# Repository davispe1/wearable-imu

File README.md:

# Wearable IMU — Project Master README

> Wearable IMU-based motion-capture system for **live upper-limb pose estimation**.
> Summer research project (IIT Chicago), with the goal of publishing.
>
> Single source of truth for the system architecture, hardware, communication design,
> processing pipeline, and repository structure.

### At a glance

| Node PCB (v1.0) | 5-DOF calibration / teleop rig |
|---|---|
|  |  |

**Left:** the wearable IMU node PCB (STM32WB55CEUx + DWM3000 + LSM6DSV16BXTR + BMM350).
**Right:** a separate parallel sub-project, [`test-rig/`](test-rig/README.md) — a
motorised 5-DOF arm used two ways: (1) **teleoperation demo**, driven live from the
wearable nodes, and (2) **calibration / ground truth**, moved through known joint
angles to validate the IMU pipeline's estimated angles against a known reference.

> **New to this project?** The actively maintained TODO / open-work list is
> [`docs/07-roadmap.md`](docs/07-roadmap.md) — start there to see what's done, what's
> open, and what's missing before picking up work.

---

## 1. Project overview

A network of small body-worn **IMU nodes** streams motion data to a **PC**, which reconstructs
and displays a live 3D skeleton of the upper limb. The design philosophy is **thin nodes,
heavy PC**: nodes only sample and transmit; all fusion, kinematics, and visualization run on
the PC — a discrete GPU is recommended for the live 3D visualization but not strictly required.

| Item | Decision (v1) |
|------|----------------|
| Focus | Upper limb |
| Output | Live joint angles + 3D skeleton visualization |
| Nodes | Scalable design; initial bring-up on **2 confirmed nodes** (wrist, clavicle), a 3rd (chest) possible, scaling to **6–8** |
| Sample rate | **100 Hz** target (hardware capable to 200 Hz) |
| Environment | Lab / bench (PC present in the room) |
| Compute | All heavy processing on the PC, **not** on a body MCU |
| Reference work | *Ultra Inertial Poser* (UIP), SIGGRAPH 2024 — see [References](#10-references) |

---

## 2. System architecture

All nodes use **identical hardware** (STM32WB55CEUx + DWM3000). One node is designated the
**master** purely in firmware. Because the boards are identical, multiple transport
topologies can be tested and compared on the same hardware (a useful experimental result).

### Primary topology

```mermaid
flowchart LR
    subgraph Body["On-body (wearable)"]
        N1["Sensor node 1<br/>WB55CE + DWM3000"]
        N2["Sensor node 2<br/>WB55CE + DWM3000"]
        N3["Sensor node N<br/>WB55CE + DWM3000"]
        M["Master node<br/>WB55CE + DWM3000"]
        N1 -- UWB --> M
        N2 -- UWB --> M
        N3 -- UWB --> M
    end
    M -- "BLE" --> PC["PC<br/>all processing + 3D viewer"]
    M -. "SWD / SWO (wired dev/recovery)" .-> PC
```

- **On-body UWB network** carries node data to the master, provides **time sync**, and
  (phase 2) provides **inter-node ranging** for drift correction.
- **Master node** aggregates all node data and is the single uplink to the PC.
- **PC** runs the full pipeline and the live visualization (stages detailed in [§6](#6-processing-pipeline-pc)).

> **v1 needs no Kalman filter.** Orientation → joint angles → DH skeleton → render is a
> complete working visualization. The EKF (with UWB distances) is a phase-2 enhancement
> for drift and position.

---

## 3. Transports & fallbacks

Every node has **two radios**: UWB for the on-body network (node → master, time sync,
ranging) and BLE for the master's wireless uplink to the PC. Paths to the PC:

| Layer | Path | Role |
|-------|------|------|
| Live | BLE (master → PC, **host-native** Bluetooth) | Main wireless link |
| Wired | **SWD / SWO** via ST-LINK, or native USB (CDC) | Bench/dev + data recovery |

Notes:
- BLE uses **serial-over-BLE** (a transparent UART-style GATT service / NUS-equivalent), so
  it behaves like a wireless UART. **Decided: host-native Bluetooth** — the PC's own
  Bluetooth receives it, no extra receiver hardware.
- **Debug/data connection is a TC2030-IDC footprint** — bare pogo-pin pads on the PCB, not a
  soldered connector. A separate Tag-Connect TC2030 cable/clip clamps onto those pads from
  outside the board (to an ST-LINK) to make contact. Carries SWDIO/SWDCLK/SWO; SWO gives a
  one-way MCU→PC data channel (read via SWV tooling).
- **USB-C carries both charging and native USB data** (the WB55CEUx has native USB; a USB
  CDC stack is already in `firmware/USB_Device/`). The bring-up smoke test is likely read
  over this USB-CDC port, not SWO — **needs confirming**, since earlier wording assumed
  SWD/SWO was the only wired data path.
- RAM ring buffer (~seconds) covers jitter/retransmit; a >3–5 s dropout is treated as a
  compromised session regardless, so heavy persistence is unnecessary.

---

## 4. Hardware — Node BOM

Single identical board for every node. The architecturally significant parts:

| Function | Part | Notes |
|----------|------|-------|
| MCU | **STM32WB55CEUx** (UFQFPN48) | Dual-core: Cortex-M4 @ 64 MHz (application) + Cortex-M0+ @ 32 MHz (radio stack), Bluetooth 5.4 LE + 802.15.4, 512 KB flash, 256 KB SRAM, native USB. Drives DWM3000 over SPI. |
| IMU | **LSM6DSV16BXTR** | 6-axis, onboard SFLP sensor fusion. **I2C1, addr `0x6B`** (SDO pulled high) |
| Magnetometer | **BMM350** | Separate 3-axis → makes the node 9-DOF. **Decided: using it for v1** (not yet implemented in firmware — see [§7](#7-build-phases--roadmap)). **I2C1, addr `0x14`** (ADSEL pulled low) |
| UWB | **DWM3000** | Data transport + sync + (phase-2) inter-node ranging. SPI1 (only SPI sensor on the node — IMU and mag are both I2C) |

Full parts list (power management, connectors, battery, indicator, etc.) is in
[`hardware/electronics/v1.0/README.md`](hardware/electronics/v1.0/README.md#key-parts),
sourced directly from the fabricated board's BOM.

### PC-side hardware

| Function | Part | Notes |
|----------|------|-------|
| BLE receiver | **PC-native Bluetooth** | No extra receiver hardware |
| Compute | Any PC (a discrete GPU helps for the live 3D visualization, not required) | Runs full pipeline + visualization |

### Node PCB v1.0 — renders & board views

> Full detail (all four copper layers, schematic PDF, fab files) lives in
> [`hardware/electronics/v1.0/`](hardware/electronics/v1.0/README.md).
> Known antenna keepout issue on the DWM3000 — see [§7](#7-build-phases--roadmap) for the
> decision on whether that becomes a v1.1 bug-fix spin or gets folded into a v2.0 redesign,
> pending v1.0 bring-up results. See also
> [`hardware/electronics/CHANGELOG.md`](hardware/electronics/CHANGELOG.md).

| PCB 3D — top | PCB 3D — bottom |
|---|---|
|  |  |

| Assembled (exploded) | Worn on wrist |
|---|---|
|  |  |

---

## 5. Communication & protocols

### Data format (per node, per sample)
- **Option A (preferred for the rig): raw 9-DOF** — accel(3) + gyro(3) + mag(3) + timestamp.
  Maximum flexibility; host does all fusion. ~40 bytes/sample.
- **Option B: SFLP quaternion** (from the LSM6DSV16B) + raw mag. Smaller, less host work.
- **Decision: open** (see [Open items](#11-open-items)). Magnetometer rate can be lower
  (e.g., 50–100 Hz).

> Bandwidth budgeting and UWB TDMA scheduling design used to be spelled out here with
> specific numbers, but neither BLE nor UWB has actually been tested on hardware yet — those
> numbers were pre-hardware-test estimates, not decisions. They now live in
> [`docs/04-firmware.md`](docs/04-firmware.md#tdma-frame-planned--not-implemented) (UWB
> scheduling/sync) and [`docs/03-communication.md`](docs/03-communication.md#6-bandwidth-check)
> (bandwidth), clearly marked as unvalidated estimates rather than settled numbers.

---

## 6. Processing pipeline (PC)

| Stage | Purpose | Maps to known technique |
|-------|---------|--------------------------|
| 0. Calibration | Sensor-to-segment alignment (T/N-pose) | — |
| 1. Orientation filter | accel+gyro(+mag) → world-frame quaternion | complementary / Madgwick / VQF (or use SFLP) |
| 2. Joint angles | relative rotation between adjacent segments | rotation matrices / quaternions |
| 3. EKF (phase 2) | fuse UWB inter-node distances → fix drift / get positions | Kalman filter (new) |
| 4. Forward kinematics | joint angles + segment lengths → 3D skeleton | **Denavit-Hartenberg** |
| 5. Visualization | live render of links/joints | 3D viewer |

- **v1 path:** stages 0 → 1 → 2 → 4 → 5 (no EKF).
- **Phase 2:** insert stage 3 (EKF + UWB ranging) for drift/position.
- A **synthetic data generator** (or arm-simulator rig) can drive the pipeline before
  hardware is ready.

---

## 7. Build phases / roadmap

1. **Firmware + data path** — node sampling, UWB schedule, master aggregation, PC ingest.
   Bring up over **SWD/SWO (wired)** first (familiar tooling), then add BLE as a parallel path.
2. **Visualization program** — orientation → joint angles → DH skeleton → live 3D render.
   Develop against **synthetic data** first. No Kalman filter needed.
3. **EKF** — learn the Kalman filter (from complementary-filter intuition) and fold in the
   UWB inter-node distances for drift/position.

> BLE de-risking: prove the entire system over wired (SWD/SWO) first; learn BLE in isolation
> on a NUCLEO-WB55RG with ST's serial-over-BLE example; then integrate with the wired path
> still available as a safety net.

### Parallel workstream — 5-DOF arm / test rig

A 5-DOF robotic arm mirroring human upper-limb kinematics. It's a single physical
rig serving **two purposes**:

1. **Teleoperation demo** — drive the arm live from the wearable IMU nodes.
2. **Calibration / ground-truth measurement** — move the arm through known joint
   angles and compare against the IMU pipeline's estimated angles, to quantify
   filter error.

Status: forward kinematics validated (MATLAB GUI); inverse kinematics implemented
but not yet validated; mechanical CAD for the rig itself in progress. Full detail
in [`docs/07-roadmap.md`](docs/07-roadmap.md#parallel-workstream--5-dof-arm-teleoperation--calibration-rig)
and [`test-rig/README.md`](test-rig/README.md).

---

## 8. Repository structure

Actual current tree (not aspirational — status noted per folder):

```
wearable-imu/
├── README.md                      # this file
├── CONTRIBUTING.md                # branch/tag/versioning conventions
├── docs/                          # markdown source of truth, one file per section
│   ├── 01-system-overview.md
│   ├── 02-hardware.md
│   ├── 03-communication.md        # authoritative wire protocol spec
│   ├── 04-firmware.md             # firmware architecture: CubeMX project + smoke test are
│   │                               #   real; packet/comms application layer still planned
│   ├── 05-host-pipeline.md
│   ├── 06-calibration.md
│   ├── 07-roadmap.md              # build phases, real done/not-done status, open items
│   ├── 08-appendices.md
│   └── 09-tools.md                # tools used to build/assemble hardware — incomplete
│
├── firmware/                      # STM32CubeIDE project for the STM32WB55CEUx node
│   ├── Core/                      # CubeMX-generated (HAL, startup, clock) — do not hand-edit
│   ├── Drivers/                   # CMSIS + STM32WBxx HAL
│   ├── Middlewares/ST/            # ST middleware
│   ├── ThirdParty/                # BMM350, lsm6dsv16bx vendor drivers
│   ├── USB_Device/                # USB CDC (virtual COM port) stack — native USB, not charging-only
│   └── *.ioc / *.ld               # CubeMX config + linker scripts
│   (application logic — packet serializer, UWB TDMA, BLE serial, role state
│    machines — not written yet; see docs/07-roadmap.md)
│
├── host/                          # Python package — the live PC pipeline
│   └── wearable_imu/
│       ├── ingest/                # serial / SWO readers + wire protocol codec (real, tested)
│       ├── sync/                  # timebase alignment
│       ├── orientation/           # filters (complementary / Madgwick / VQF) — stub
│       ├── kinematics/            # joint angles + DH forward kinematics — stub
│       ├── ekf/                   # phase 2: UWB-distance fusion — stub
│       ├── viz/                   # 3D skeleton viewer — stub
│       ├── sim/                   # synthetic data generator (real, drives dev without hardware)
│       ├── config.py
│       └── main.py
│
├── hardware/                      # physical design files — only place with version folders
│   ├── electronics/v1.0/          # node PCB: schematic, layout, fab files, renders
│   └── mechanical/v1.0/           # node enclosure: STEP/STL, assembly renders
│
├── simulation/scripts/            # 5-DOF arm kinematics (MATLAB) — FK validated, IK
│                                   # implemented pending validation. Not yet cross-linked
│                                   # into test-rig/ below.
├── test-rig/                      # ground-truth validation rig — mostly planned
│   └── hardware/mechanical/v1.0/  # rig arm CAD — in progress (the only real part so far)
│
├── calibration/                   # calibration routines + saved profiles — planned
└── tools/                         # flash/capture/calibrate/replay scripts — planned
```

---

## 9. Design decisions log (the "why")

- **Sensor selection, generally:** across the BOM, the guiding principle was to pick the
  most capable part available in its class at design time, not the cheapest one that
  technically works — this is a research/publication project, not a cost-optimized
  product, so headroom (accuracy, noise floor, ranging precision) was prioritized over
  BOM cost. The three sensing ICs below were each chosen on that basis:
  - **IMU = LSM6DSV16BXTR:** one of ST's most capable 6-axis parts at selection time —
    onboard SFLP (Sensor Fusion Low Power) hardware fusion can offload orientation
    estimation from the host, but is bypassable for a raw-data path if the host EKF is
    preferred instead. High ODR headroom (only 120 Hz is used here).
  - **Magnetometer = BMM350:** chosen for resolution/noise performance over cheaper
    3-axis parts, making the node 9-DOF. Populated on every board, but use is **optional**
    pending characterization of the lab's magnetic environment — indoor steel/motors can
    make magnetometer data actively worse than leaving it out.
  - **UWB = DWM3000:** the most capable UWB module available for this application —
    supports the newer 802.15.4z standard (better multipath resistance) with strong
    ranging accuracy. Chosen as the **sole radio** on the node: it replaces what would
    otherwise be a separate ranging radio, handling data transport, sub-ns time sync,
    and inter-node ranging in one part.
- **MCU = STM32WB55CEUx** (over the earlier L431 / U535): the master needs BLE; identical
  BLE-capable boards let any node be master and enable topology testing. Dual-core
  (Cortex-M4 app core + Cortex-M0+ radio stack core), ultra-low-power (good for a small
  battery), and has native USB (unlike the STM32WBA55 originally assumed during design —
  see the note in [§3](#3-transports--fallbacks) about reconciling the SWD/SWO-vs-USB wired
  data path now that native USB is actually available).
- **Master-aggregator + single BLE uplink** (vs UIP's per-node BLE): one BLE link instead of
  N (avoids PC multi-link flakiness) and gives tighter on-body sync.
- **BLE for the PC uplink, UWB kept on-body:** the master's single link to the PC is BLE
  (2.4 GHz, more robust to body blocking than UWB's 6.5–8 GHz); UWB is reserved for the
  on-body network — data transport to the master, time sync, and ranging — where it's
  irreplaceable.
- **PC does all heavy compute** (not a body MCU): the pipeline (and future ML) is GPU/
  desktop work, and PC-side iteration is far faster than reflashing firmware.
- **No on-node SD card or flash IC:** RAM buffer only; avoids tedious card extraction, and
  the fabricated v1.0 board doesn't populate a flash chip at all — recovery happens over
  SWD (or USB, pending the reconciliation above).
- **100 Hz for v1:** matches UIP and is sufficient for full-body pose; keeps BLE bandwidth
  comfortable.

---

## 10. References

- **[Ultra Inertial Poser (UIP), SIGGRAPH 2024](https://siplab.org/projects/UltraInertialPoser)**
  (Armani, Qian, Jiang, Holz — [ACM DL](https://dl.acm.org/doi/10.1145/3641519.3657465),
  [arXiv](https://arxiv.org/abs/2404.19541),
  [code](https://github.com/eth-siplab/UltraInertialPoser)) — sparse body-worn IMU + UWB
  inter-node ranging, fused on a host with VQF orientation, per-pair EKF, an LSTM + graph-conv
  network, and a physics dynamics optimizer to produce full-body pose.
  - **This project mirrors** the IMU + UWB sensing approach and the "thin nodes, host does
    the work" philosophy.
  - **This project differs:** adds a magnetometer (9-DOF vs UIP's 6-DoF); uses a
    master-aggregator UWB→BLE topology (vs UIP's per-node BLE to host); focuses on upper-limb
    joint angles + live visualization for v1; EKF/ranging is a phase-2 enhancement.

---

## 11. Open items

**The actively maintained TODO / open-work list lives in
[`docs/07-roadmap.md`](docs/07-roadmap.md)** — its "Open items", "Hardware revisions", and
"Known gaps" sections are the source of truth for what's decided, what's still open, and
what's missing (including firmware, UWB/BLE testing, the test-rig end-effector adapter, and
the onboarding doc for new students). This section is intentionally just a short pointer
rather than a second list, to avoid the two drifting out of sync.

Top-level decisions still open, at a glance:
- **Data format:** raw 9-DOF vs SFLP quaternion + raw mag.
- **Magnetometer:** whether to use it (characterize the lab's magnetic environment first;
  hardware is populated either way).
- **Sample rate:** confirm 100 Hz (vs 200 Hz).

---

## How to use this document

This README and the `docs/` folder are the **markdown source of truth** (versioned in git;
diagrams in **Mermaid** so they edit as text and render on GitHub). For a polished copy for
the team/professor, export markdown → Word/PDF with Pandoc rather than hand-maintaining a
second copy.

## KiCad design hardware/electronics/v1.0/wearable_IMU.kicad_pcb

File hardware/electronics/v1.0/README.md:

# electronics / v1.0

Node PCB — revision 1.0. 4-layer board (F.Cu, In1.Cu, In2.Cu, B.Cu).

> **Known issue, fix path pending v1.0 evaluation:** the DWM3000 UWB antenna
> placement doesn't fully follow Qorvo's layout guidelines (clearance/keepout,
> feed line length), which may affect range/link margin. Whether this becomes a
> v1.1 placement-only fix or gets folded into a v2.0 redesign depends on how
> v1.0 performs in bring-up. See `../CHANGELOG.md` and `docs/07-roadmap.md`.

## Contents

- `wearable_IMU.kicad_sch` — schematic (source)
- `wearable_IMU.kicad_pcb` — layout (source)
- `wearable_IMU.kicad_pro` / `.kicad_prl` — project files
- `documentation/` — exported images (below) + `schematic.pdf`
- `jlcpcb/` — fab outputs: `gerber/` (raw Gerbers + drill files), `production_filesV1.0/`
  (BOM, pick-and-place, zipped Gerbers — the JLCPCB submission set), `project.db`
- `fabrication-toolkit-options.json` — KiCad fabrication-toolkit plugin export settings
- The PCB's 3D model (`PCB.step`) lives in `../../mechanical/v1.0/` alongside the
  enclosure — kept in one place instead of duplicated here

Cleaned up (untracked, safe to regenerate/ignore): KiCad's local autosave/history
folders (`.history/`, `.history_trim/` — an embedded git history plugin, ~290 MB),
`wearable_IMU-backups/` (autosave zips), a stale `production/` test export
("prueba1"), an empty `jlcpcb/production_files/`, 0-byte `.rpt` temp files, and
KiCad's `.lck` lock files. Added patterns to `.gitignore` so these don't come back.

## Key parts

Straight from the fabricated board's BOM (`jlcpcb/production_filesV1.0/BOM-wearable_IMU.csv`):

| Function | Part |
|----------|------|
| MCU | STM32WB55CEUx |
| IMU | LSM6DSV16BXTR |
| Mag | BMM350 |
| UWB | DWM3000 |
| SMPS | TPSM828224 |
| Charger | BQ25185 |
| Fuel gauge | MAX17048G+T10 |
| Power btn | STM6601BM2DDM6F |

No flash IC is populated — RAM buffering only, no on-node session logging.

## Fabrication

Board fabricated and assembled via **JLCPCB** (PCBA — SMT assembly included, not just bare
board fab). Production files were exported from KiCad using the **fabrication-toolkit**
plugin (`fabrication-toolkit-options.json` holds its export settings).

To re-order or fab a new revision:
1. Open `wearable_IMU.kicad_pro` in KiCad, update as needed.
2. Run the fabrication-toolkit plugin to regenerate `jlcpcb/production_filesV1.0/` (or a new
   `production_filesVX.Y/` for a new revision) — Gerbers, `BOM-wearable_IMU.csv`,
   `CPL-wearable_IMU.csv` (component placement).
3. Upload the zipped Gerbers + BOM + CPL to JLCPCB's PCBA order flow.

## Board renders & layers

**3D views**

| Top | Bottom |
|---|---|
|  |  |

**Copper layers** (top → bottom of stack)

| F.Cu (top) | In1.Cu | In2.Cu | B.Cu (bottom) |
|---|---|---|---|
|  |  |  |  |

**Schematic:** [`documentation/schematic.pdf`](documentation/schematic.pdf)

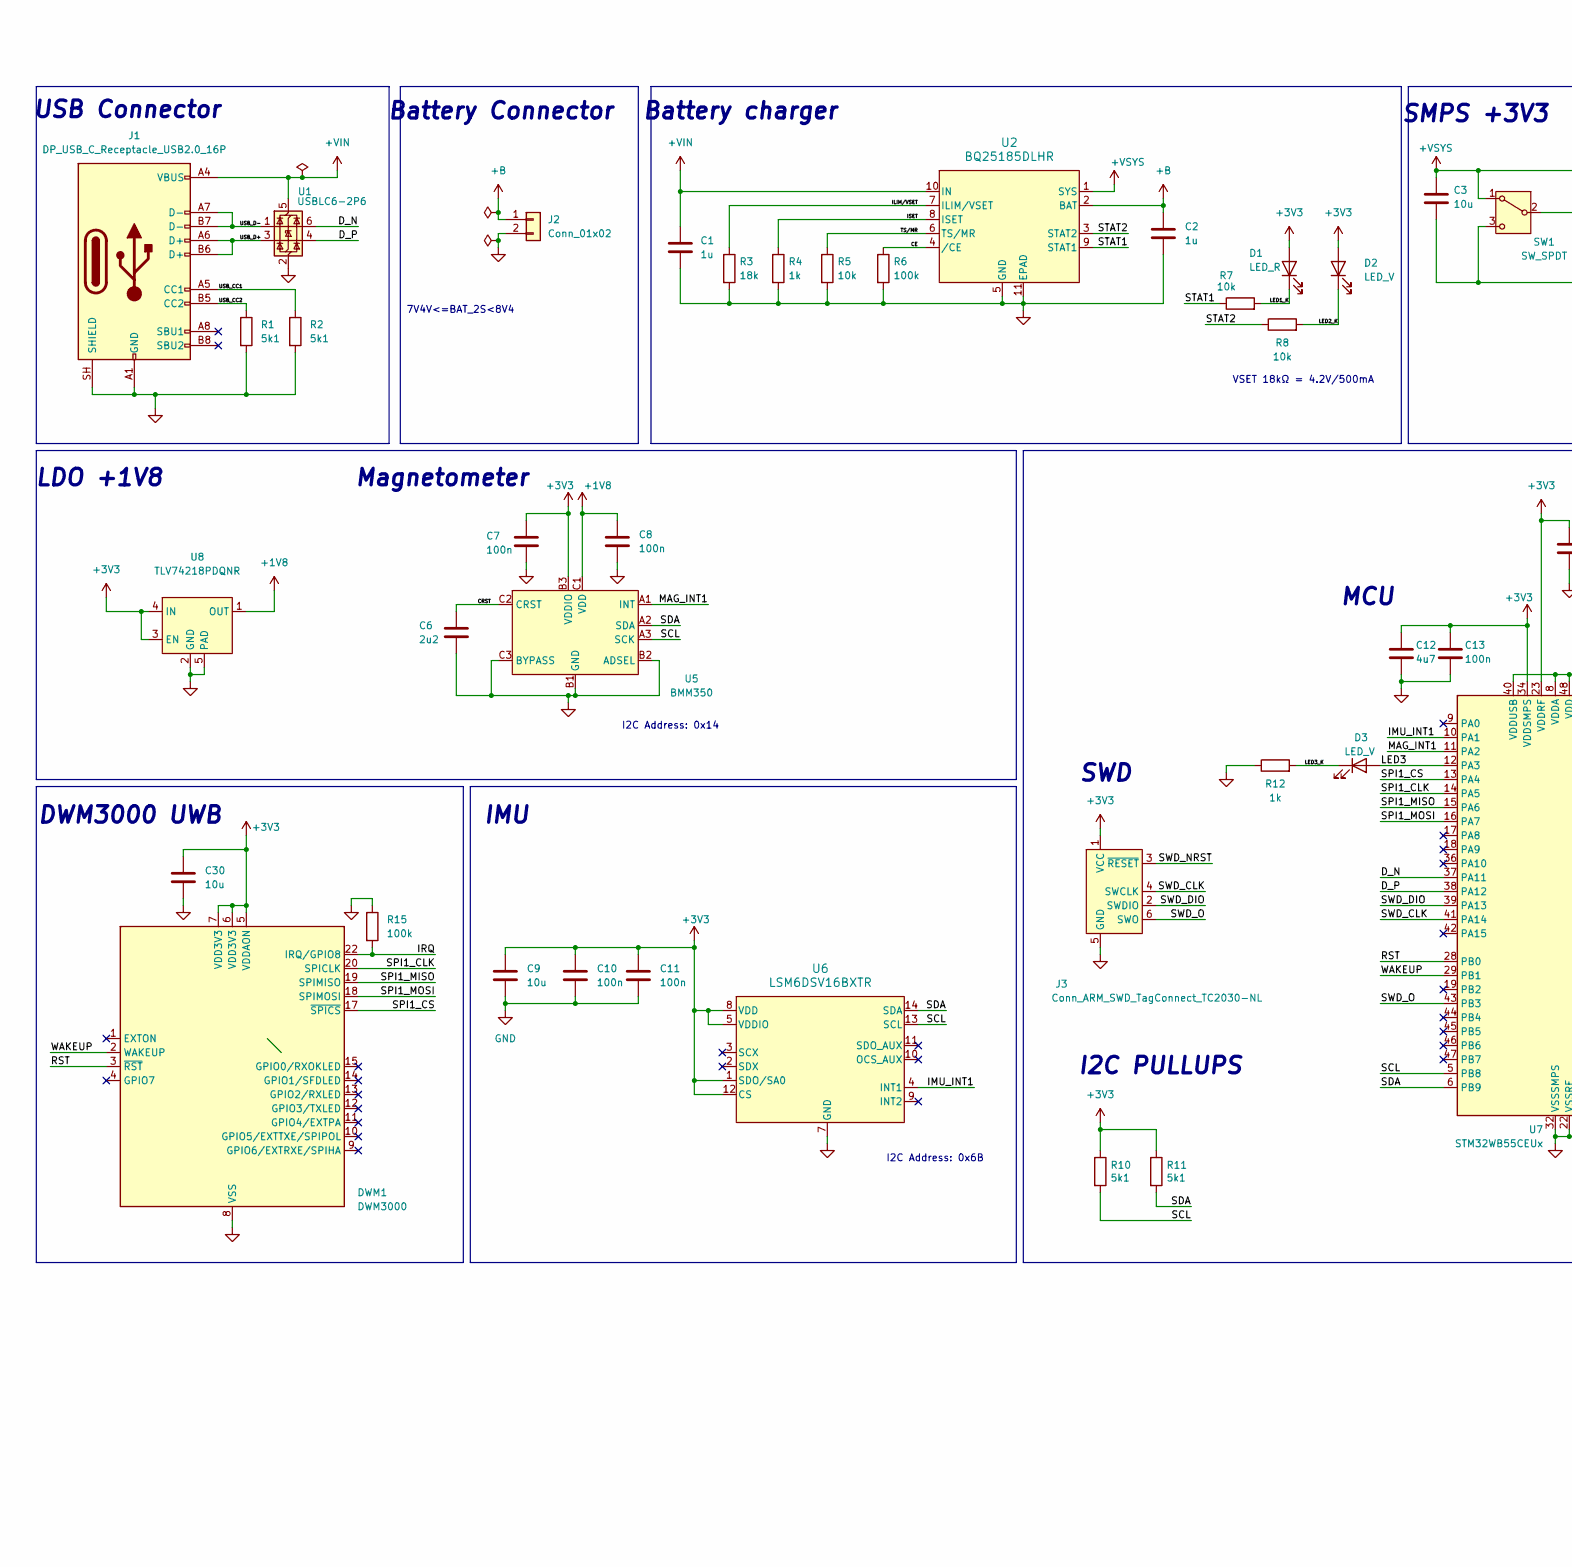
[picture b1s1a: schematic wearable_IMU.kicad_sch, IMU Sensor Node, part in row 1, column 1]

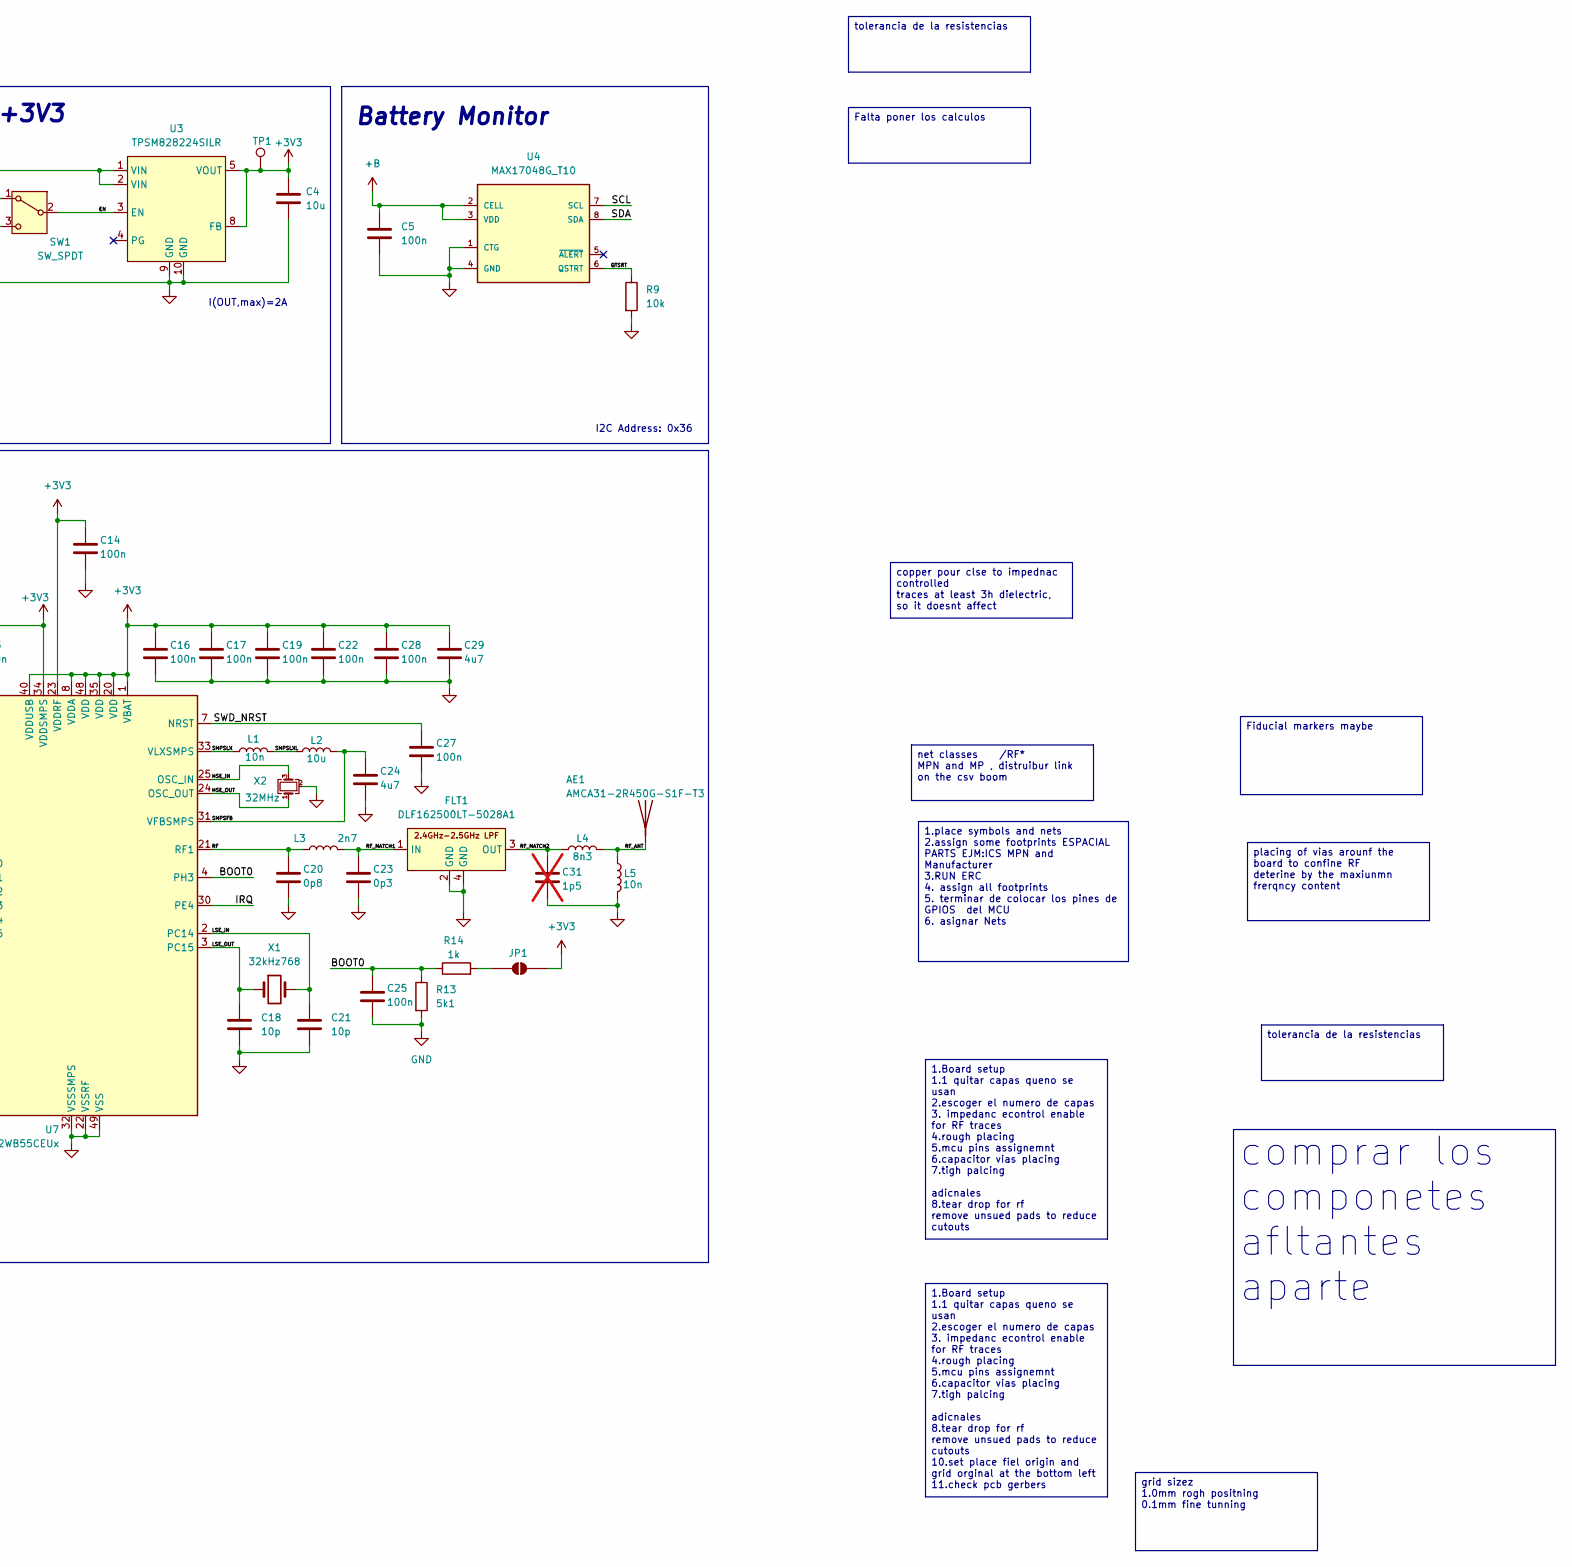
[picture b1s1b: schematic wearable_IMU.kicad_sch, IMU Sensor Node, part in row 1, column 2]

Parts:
AE1: AMCA31-2R450G-S1F-T3; XDCR_AMCA31-2R450G-S1F-T3; MPN AMCA31-2R450G-S1F-T3
C1, C2: 1u; C_0402_1005Metric
C3, C4, C9, C30: 10u; C_0603_1608Metric
C5, C7, C8, C10, C11, C13, C14, C16, C17, C19, C22, C25, C27, C28: 100n; C_0402_1005Metric
C6: 2u2; C_0402_1005Metric; MPN 0805YC225KAT2A
C12, C29: 4u7; C_0603_1608Metric
C18, C21: 10p; C_0402_1005Metric
C20: 0p8; C_0402_1005Metric; MPN GRM1555C1HR80BA01D
C23: 0p3; C_0402_1005Metric; MPN GRM1555C1HR30WA01D
C24: 4u7; C_0603_1608Metric; MPN GRM155R60J475KE19
C31: 1p5; C_0402_1005Metric; not fitted
D1: LED_R; LED_0402_1005Metric
D2, D3: LED_V; LED_0402_1005Metric
DWM1: DWM3000; MPN DWM3000TR13
FLT1: DLF162500LT-5028A1; FILTER-SMD_0603-4P-L1.6-W0.8-L-1; MPN DLF162500LT-5028A1; LCSC Part C531364
J1: DP_USB_C_Receptacle_USB2.0_16P; DP_USB_C_Receptacle_GCT_USB4105-xx-A_16P_TopMnt_Horizontal
J2: Conn_01x02; JST_SH_SM02B-SRSS-TB_1x02-1MP_P1.00mm_Horizontal
J3: Conn_ARM_SWD_TagConnect_TC2030-NL; Tag-Connect_TC2030-IDC-NL_2x03_P1.27mm_Vertical
JP1: SolderJumper_2_Open; SolderJumper-2_P1.3mm_Open_RoundedPad1.0x1.5mm
L1: 10n; L_0402_1005Metric; LCSC Part C445746
L2: 10u; L_0805_2012Metric; MPN LQM21FN100M70L; LCSC Part C162582
L3: 2n7; L_0402_1005Metric; LCSC Part C113054
L4: 8n3; L_0402_1005Metric; MPN LQW15AN8N3C10D; LCSC Part C412363
L5: 10n; L_0402_1005Metric; MPN LQW15AN9N7G00D; LCSC Part C269828
R1, R2, R10, R11, R13: 5k1; R_0402_1005Metric
R3: 18k; R_0402_1005Metric
R4, R12, R14: 1k; R_0402_1005Metric
R5, R7, R8, R9: 10k; R_0402_1005Metric
R6, R15: 100k; R_0402_1005Metric
SW1: SW_SPDT; SW-SMD_MST-12D18G4-SPDT-SLIDE-SWITCH
TP1: TestPoint; TestPoint_Pad_D1.5mm
U1: USBLC6-2P6; SOT-666
U2: BQ25185DLHR; WSON10_DLH_TEX; MPN BQ25185DLHR; DigiKey_Part_Number 296-BQ25185DLHRCT-ND
U3: TPSM828224SILR; USIP-10_L2.5-W2.0-P0.50-BL; MPN TPSM828224SILR; LCSC Part C2862913
U4: MAX17048G_T10; DFN-8-1EP_2x2mm_P0.5mm_EP0.9x1.3mm; MPN IC BATT MON LI-ION 1CELL 8TDFN; LCSC Part C2682616
U5: BMM350; DP_WLCSP-9_1.21x1.22mm_Layout3x3_P0.4mm; MPN BMM350; LCSC Part C17225907
U6: LSM6DSV16BXTR; LGA-14_3x2.5mm_P0.5mm_LayoutBorder3x4y; MPN LSM6DSV16BXTR
U7: STM32WB55CEUx; QFN-48-1EP_7x7mm_P0.5mm_EP5.6x5.6mm; MPN STM32WB55CEU6
U8: TLV74218PDQNR; X2SON-4_L1.0-W1.0-P0.65-BL-EP; MPN TLV74218PDQNR; LCSC Part C485140
X1: 32kHz768; Crystal_SMD_2012-2Pin_2.0x1.2mm; MPN NX2016_32M; LCSC Part C891748
X2: 32MHz; Crystal_SMD_2016-4Pin_2.0x1.6mm; MPN NX2016SA-32M-EXS00A-CS06465; LCSC Part C1986260

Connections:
+1V8: C8.1, U5.C1 (VDD), U8.1 (OUT)
+3V3: C4.1, C7.1, C9.1, C10.1, C11.1, C12.1, C13.1, C14.1, C16.1, C17.1, C19.1, C22.1, C28.1, C29.1, C30.1, D1.2 (A), D2.2 (A), DWM1.5 (VDDAON), DWM1.6 (VDD3V3), DWM1.7 (VDD3V3), J3.1 (VCC), JP1.2 (B), R10.1, R11.1, TP1.1 (1_1), U3.5 (VOUT), U3.6 (VOUT), U3.7 (VOUT), U3.8 (FB), U5.B3 (VDDIO), U6.1 (SDO/SA0), U6.5 (VDDIO), U6.8 (VDD), U6.12 (CS), U7.1 (VBAT), U7.8 (VDDA), U7.20 (VDD), U7.23 (VDDRF), U7.34 (VDDSMPS), U7.35 (VDD), U7.40 (VDDUSB), U7.48 (VDD), U8.3 (EN), U8.4 (IN)
+B: C2.1, C5.1, J2.1, U2.2 (BAT), U4.2 (CELL), U4.3 (VDD)
+VIN: C1.1, J1.A4 (VBUS), J1.A9 (VBUS), J1.B4 (VBUS), J1.B9 (VBUS), U1.5 (VBUS), U2.10 (IN)
+VSYS: C3.1, SW1.1 (A), U2.1 (SYS), U3.1 (VIN), U3.2 (VIN)
/BOOT0: C25.1, R13.1, R14.1, U7.4 (PH3)
/CE: R6.1, U2.4 (/CE)
/CRST: C6.1, U5.C2 (CRST)
/D_N: U1.6 (I/O1), U7.37 (PA11)
/D_P: U1.4 (I/O2), U7.38 (PA12)
/EN: SW1.2 (B), U3.3 (EN)
/HSE_IN: U7.25 (OSC_IN), X2.3
/HSE_OUT: U7.24 (OSC_OUT), X2.1
/ILIM/VSET: R3.1, U2.7 (ILIM/VSET)
/IMU_INT1: U6.4 (INT1), U7.10 (PA1)
/IRQ: DWM1.22 (IRQ/GPIO8), R15.2, U7.30 (PE4)
/ISET: R4.1, U2.8 (ISET)
/LED1_K: D1.1 (K), R7.2
/LED2_K: D2.1 (K), R8.2
/LED3: D3.2 (A), U7.12 (PA3)
/LED3_K: D3.1 (K), R12.2
/LSE_IN: C21.1, U7.2 (PC14), X1.2
/LSE_OUT: C18.1, U7.3 (PC15), X1.1
/MAG_INT1: U5.A1 (INT), U7.11 (PA2)
/QTSRT: R9.1, U4.6 (QSTRT)
/RF: C20.1, L3.1, U7.21 (RF1)
/RF_ANT: AE1.1 (A_1), L4.2, L5.1
/RF_MATCH1: C23.1, FLT1.1 (IN), L3.2
/RF_MATCH2: C31.1, FLT1.3 (OUT), L4.1
/RST: DWM1.3 (~RST), U7.28 (PB0)
/SCL: R10.2, U4.7 (SCL), U5.A3 (SCK), U6.13 (SCL), U7.5 (PB8)
/SDA: R11.2, U4.8 (SDA), U5.A2 (SDA), U6.14 (SDA), U7.6 (PB9)
/SMPSFB: C24.1, L2.2, U7.31 (VFBSMPS)
/SMPSLX: L1.1, U7.33 (VLXSMPS)
/SMPSLXL: L1.2, L2.1
/SPI1_CLK: DWM1.20 (SPICLK), U7.14 (PA5)
/SPI1_CS: DWM1.17 (~SPICS), U7.13 (PA4)
/SPI1_MISO: DWM1.19 (SPIMISO), U7.15 (PA6)
/SPI1_MOSI: DWM1.18 (SPIMOSI), U7.16 (PA7)
/STAT1: R7.1, U2.9 (STAT1)
/STAT2: R8.1, U2.3 (STAT2)
/SWD_CLK: J3.4 (SWCLK), U7.41 (PA14)
/SWD_DIO: J3.2 (SWDIO), U7.39 (PA13)
/SWD_NRST: C27.1, J3.3 (~RESET), U7.7 (NRST)
/SWD_O: J3.6 (SWO), U7.43 (PB3)
/TS/MR: R5.1, U2.6 (TS/MR)
/USB_CC1: J1.A5 (CC1), R2.1
/USB_CC2: J1.B5 (CC2), R1.1
/USB_D+: J1.A6 (D+), J1.B6 (D+), U1.3 (I/O2)
/USB_D-: J1.A7 (D-), J1.B7 (D-), U1.1 (I/O1)
/WAKEUP: DWM1.2 (WAKEUP), U7.29 (PB1)
GND: C1.2, C2.2, C3.2, C4.2, C5.2, C6.2, C7.2, C8.2, C9.2, C10.2, C11.2, C12.2, C13.2, C14.2, C16.2, C17.2, C18.2, C19.2, C20.2, C21.2, C22.2, C23.2, C24.2, C25.2, C27.2, C28.2, C29.2, C30.2, C31.2, DWM1.8 (VSS), DWM1.16 (VSS), DWM1.21 (VSS), DWM1.23 (VSS), DWM1.24 (VSS), FLT1.2 (GND), FLT1.4 (GND), J1.A1 (GND), J1.A12 (GND), J1.B1 (GND), J1.B12 (GND), J1.SH (SHIELD), J2.2, J3.5 (GND), L5.2, R1.2, R2.2, R3.2, R4.2, R5.2, R6.2, R9.2, R12.1, R13.2, R15.1, SW1.3 (C), U1.2 (GND), U2.5 (GND), U2.11 (EPAD), U3.9 (GND), U3.10 (GND), U4.1 (CTG), U4.4 (GND), U4.9 (EP), U5.B1 (GND), U5.B2 (ADSEL), U5.C3 (BYPASS), U6.6 (GND), U6.7 (GND), U7.22 (VSSRF), U7.32 (VSSSMPS), U7.49 (VSS), U8.2 (GND), U8.5 (PAD), X2.2 (G), X2.4 (G)
unnamed: JP1.1 (A), R14.2

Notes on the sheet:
I2C Address: 0x14
MCU
I2C Address: 0x6B
I2C PULLUPS
VSET 18kΩ = 4.2V/500mA
SWD
IMU
Battery charger
7V4V<=BAT_2S<8V4
Battery Monitor
SMPS +3V3
I(OUT,max)=2A
Magnetometer
LDO +1V8
USB Connector
DWM3000 UWB
Battery Connector
I2C Address: 0x36
1.Board setup 1.1 quitar capas queno se usan 2.escoger el numero de capas 3. impedanc econtrol enable for RF traces 4.rough placing 5.mcu pins assignemnt 6.capacitor vias placing 7.tigh palcing adicnales 8.tear drop for rf remove unsued pads to reduce cutouts 10.set place fiel origin and grid orgin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
net classes /RF* MPN and MP , distruibur link on the csv boom
Falta poner los calculos
Fiducial markers maybe
tolerancia de la resistencias
placing of vias arounf the board to confine RF deterine by the maxiunmn frerqncy content
1.Board setup 1.1 quitar capas queno se usan 2.escoger el numero de capas 3. impedanc econtrol enable for RF traces 4.rough placing 5.mcu pins assignemnt 6.capacitor vias placing 7.tigh palcing adicnales 8.tear drop for rf remove unsued pads to reduce cutouts
1.place symbols and nets 2.assign some footprints ESPACIAL PARTS EJM:ICS MPN and Manufacturer 3.RUN ERC 4. assign all footprints 5. terminar de colocar los pines de GPIOS del MCU 6. asignar Nets
comprar los componetes afltantes aparte
copper pour clse to impednac controlled traces at least 3h dielectric, so it doesnt affect
grid sizez 1.0mm rogh positning 0.1mm fine tunning

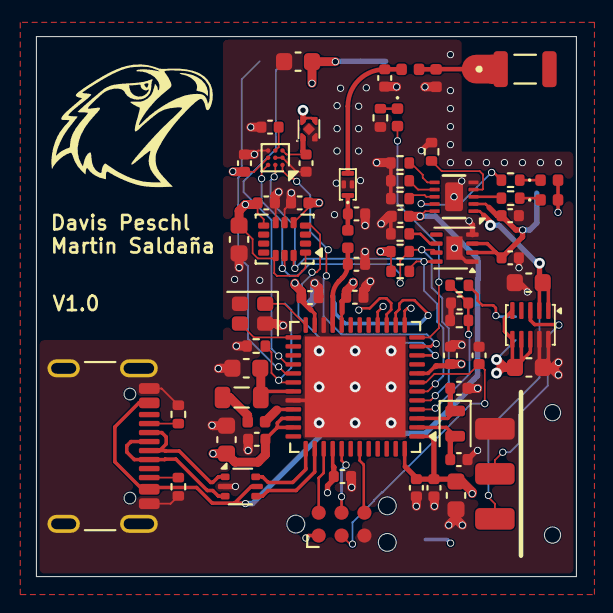
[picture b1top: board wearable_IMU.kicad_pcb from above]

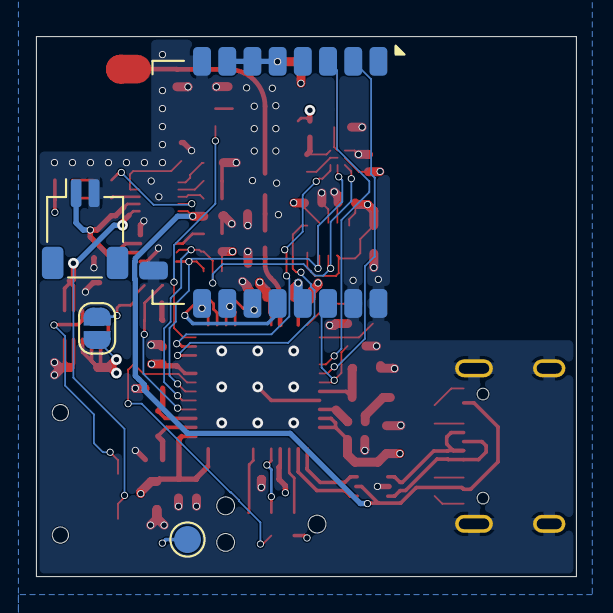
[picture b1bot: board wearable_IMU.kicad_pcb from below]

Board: 4 copper layers, 30.0 x 30.0 mm, 72 parts (4 on the bottom side), 53 nets.

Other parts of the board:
G1: LOGO; IIT

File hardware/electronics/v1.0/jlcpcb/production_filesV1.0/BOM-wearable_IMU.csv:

Comment,Designator,Footprint,LCSC,Quantity
0p3,C23,C_0402_1005Metric,C76909,1
0p8,C20,C_0402_1005Metric,C3859264,1
100k,"R15,R6",R_0402_1005Metric,C25741,2
100n,"C10,C11,C13,C14,C16,C17,C19,C22,C25,C27,C28,C5,C7,C8",C_0402_1005Metric,C307331,14
10k,"R5,R7,R8,R9",R_0402_1005Metric,C25744,4
10n,"L1,L5",L_0402_1005Metric,C77103,2
10p,"C18,C21",C_0402_1005Metric,C32949,2
10u,L2,L_0805_2012Metric,C162582,1
10u,"C3,C30,C4,C9",C_0603_1608Metric,C96446,4
18k,R3,R_0402_1005Metric,C138044,1
1k,"R12,R14,R4",R_0402_1005Metric,C11702,3
1u,"C1,C2",C_0402_1005Metric,C52923,2
2n7,L3,L_0402_1005Metric,C113054,1
2u2,C6,C_0402_1005Metric,C77002,1
32MHz,X2,Crystal_SMD_2016-4Pin_2.0x1.6mm,C1986260,1
32kHz768,X1,Crystal_SMD_2012-2Pin_2.0x1.2mm,C891748,1
4u7,"C12,C24,C29",C_0603_1608Metric,C19666,3
5k1,"R1,R10,R11,R13,R2",R_0402_1005Metric,C25905,5
8n3,L4,L_0402_1005Metric,C412363,1
AMCA31-2R450G-S1F-T3,AE1,XDCR_AMCA31-2R450G-S1F-T3,C3283994,1
BMM350,U5,DP_WLCSP-9_1.21x1.22mm_Layout3x3_P0.4mm,C17225907,1
BQ25185DLHR,U2,WSON10_DLH_TEX,C19725033,1
DLF162500LT-5028A1,FLT1,FILTER-SMD_0603-4P-L1.6-W0.8-L-1,C531364,1
DP_USB_C_Receptacle_USB2.0_16P,J1,DP_USB_C_Receptacle_GCT_USB4105-xx-A_16P_TopMnt_Horizontal,C393939,1
LED_R,D1,LED_0402_1005Metric,C25503345,1
LED_V,"D2,D3",LED_0402_1005Metric,C965793,2
LSM6DSV16BXTR,U6,LGA-14_3x2.5mm_P0.5mm_LayoutBorder3x4y,C5267394,1
MAX17048G_T10,U4,DFN-8-1EP_2x2mm_P0.5mm_EP0.9x1.3mm,C2682616,1
STM32WB55CEUx,U7,QFN-48-1EP_7x7mm_P0.5mm_EP5.6x5.6mm,C911135,1
SW_SPDT,SW1,SW-SMD_MST-12D18G4-SPDT-SLIDE-SWITCH,C49023767,1
TLV74218PDQNR,U8,X2SON-4_L1.0-W1.0-P0.65-BL-EP,C485140,1
TPSM828224SILR,U3,USIP-10_L2.5-W2.0-P0.50-BL,C2862913,1
USBLC6-2P6,U1,SOT-666,C15999,1

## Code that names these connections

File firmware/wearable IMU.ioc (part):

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Mcu.Name=STM32WB55CEUx
Mcu.Package=UFQFPN48
Mcu.UserName=STM32WB55CEUx
PA1.Signal=GPIO_Input
PA11.Mode=Device
PA11.Signal=USB_DM
PA12.Mode=Device
PA12.Signal=USB_DP
PA13.Mode=Trace_Asynchronous_SW
PA13.Signal=SYS_JTMS-SWDIO
PA14.Mode=Trace_Asynchronous_SW
PA14.Signal=SYS_JTCK-SWCLK
PA2.Signal=GPIO_Input
PA3.Signal=GPIO_Output
PA4.Signal=GPIO_Output
PA5.Mode=Full_Duplex_Master
PA5.Signal=SPI1_SCK
PA6.Mode=Full_Duplex_Master
PA6.Signal=SPI1_MISO
PA7.Mode=Full_Duplex_Master
PA7.Signal=SPI1_MOSI
PB0.Signal=GPIO_Output
PB1.Signal=GPIO_Output
PB3.Mode=Trace_Asynchronous_SW
PB3.Signal=SYS_JTDO-SWO
PB8.Mode=I2C
PB8.Signal=I2C1_SCL
PB9.Mode=I2C
PB9.Signal=I2C1_SDA
PC14-OSC32_IN.Mode=LSE-External-Oscillator
PC14-OSC32_IN.Signal=RCC_OSC32_IN
PC15-OSC32_OUT.Mode=LSE-External-Oscillator
PC15-OSC32_OUT.Signal=RCC_OSC32_OUT
PE4.Signal=GPIO_Input
RCC.HSE_VALUE=32000000
RCC.SYSCLKFreq_VALUE=64000000
RCC.SYSCLKSource=RCC_SYSCLKSOURCE_PLLCLK
board=custom

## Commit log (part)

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2026-06-16 Carga inicial: motor Gait Kinematics, app visor y configuraciones
2026-06-16 Mover todos los archivos del proyecto a una subcarpeta
2026-06-17 Gait Kinematics: gaitlib, app, pipeline, docs, ARCHITECTURE.md — clean root layout
